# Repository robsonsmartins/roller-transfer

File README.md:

# PCB Roller Transfer Machine
The PCB Roller Transfer Machine (or Laminator Machine) is a machine designed to thermally transfer toner printed on paper to a blank Printed Circuit Board.

Project site: [PCB Roller Transfer Machine Project](https://www.robsonmartins.com/content/eletr/projects/laminadora/)

[![CC BY-NC-SA 4.0][cc-by-nc-sa-shield]][cc-by-nc-sa]

This work is licensed under a
[Creative Commons Attribution-NonCommercial-ShareAlike 4.0 International License][cc-by-nc-sa].

[![CC BY-NC-SA 4.0][cc-by-nc-sa-image]][cc-by-nc-sa]

[cc-by-nc-sa]: http://creativecommons.org/licenses/by-nc-sa/4.0/
[cc-by-nc-sa-image]: https://licensebuttons.net/l/by-nc-sa/4.0/88x31.png
[cc-by-nc-sa-shield]: https://img.shields.io/badge/License-CC%20BY--NC--SA%204.0-lightgrey.svg

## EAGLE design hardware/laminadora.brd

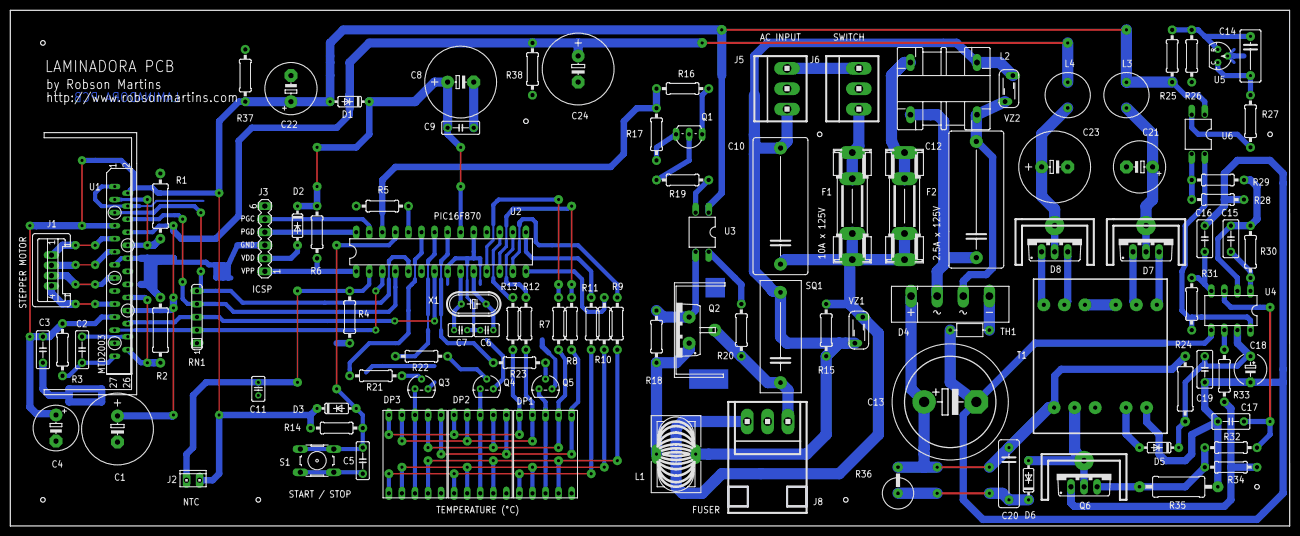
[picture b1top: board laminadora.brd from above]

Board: 2 copper layers, 248.5 x 99.9 mm, 105 parts (0 on the bottom side), 87 nets.

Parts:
C1: 2200uF x 16V; E5-13
C2: 3n3; C050-025X075
C3, C5, C9: 100nF; C050-025X075
C4: 470uF x 10V; E5-8,5
C6, C7: 15pF; C025-025X050
C8: 2200uF x 10V; E5-13
C10, C12: 220nF x 250V; C225-108X268
C11: 1nF; C025-025X050
C13: 330uF x 200V; EB22,5D
C14: 330nF; C075-042X103
C15: 2n7; C050-030X075
C16: 2n2; C050-030X075
C17: 10nF; C050-030X075
C18: 47uF x 25V; E5-6
C19: 100nF; C050-030X075
C20: 10nF x 400V; C102-043X133
C21, C22: 1000uF x 10V; E5-10,5
C23: 1000uF x 25V; E5-13
C24: 2200uF x 25V; E5-13
D1, D5, D6: 1N3613; DO35-7
D2, D3: 1N4148; DO35-7
D4: D2SBA-60; FBU4
D7, D8: F10SC4R; TO220ABS
DP1, DP2, DP3: HD-H103; HDSP-M
F1: 10A; SHK20L
F2: 2.5A; SHK20L
J1: A20-04
J2: A20-04; 10X02MTA
J3: MA06-1
J5, J6, J8: 794681-2; 1X3MTA
L1: 80uH; A26GFC
L2: MFE
L3, L4: 4.7uH; 6000-XXXX-RC
Q1: 2SC1740; TO92-ECB
Q2: BCR8PM; TO220BVSINK
Q3, Q4, Q5: BC547; TO92
Q6: FS7UM; TO220BV
R1, R2: 0R47; 0309/12
R3: 20K; 0207/10
R4: 5K6 x 1%; 0207/10
R5, R6, R14, R31: 10K; 0207/10
R7, R8, R9, R10, R11, R12, R13, R37: 100R; 0207/10
R15: 1M; 0207/10
R16: 100K; 0207/10
R17, R34: 2K2; 0207/10
R18, R19, R27: 150R; 0207/10
R20, R33: 22R; 0207/10
R21, R22, R23, R38: 1K; 0207/10
R24: 56K x 1W; 0309/12
R25, R26: 3K9 x 1%; 0207/10
R28: 270R; 0207/10
R29, R30: 3K9; 0207/10
R32: 56R; 0207/10
R35: 0R33 x 2W; 0411/15
R36: 22K x 7W; 0617V
RN1: 10K; SIL5
S1: B3F-10XX
SQ1: AU1201; AU
T1: SK69ABD2
TH1: BR207; R-7,5
U1: MTD2003; ZIP27SINK
U2: PIC16F870P; DIL28-3
U3: S21ME6; DIL4
U4: UC3842N; DIL08
U5: TL431; TO92-CLP
U6: PS2501; DIL04
VZ1, VZ2: V7471U; S05K17
X1: 20MHz; HC49U-V

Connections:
5VNR: C21.+, D7.C, L3.1
12VNR: C23.+, D8.C, L4.1
+5V: C3.1, C4.+, C22.+, D1.A, D3.C, J2.1, L3.2, R3.2, R14.2, R25.2, R37.2, U1.2, U1.7, U1.21, U3.1, U6.1
+12V: C1.+, C24.+, L4.2, R38.2, U1.8, U1.20
+150V: C13.+, C20.1, D4.+, R24.2, R36.2, T1.1
A: R7.2, U2.11
AC_COM: C10.2, J5.3, L1.1, L2.4, R15.1, SQ1.1, VZ1.1, VZ2.1
AC_FUSER: J8.3, Q2.T2, R20.2, SQ1.2
AC_IN: J5.1, J6.1
AC_OUT: C10.1, F1.2A, F2.1A, J8.1, R15.2, VZ1.2
AC_SW: F1.1A, J6.3
AGND: C13.-, C16.2, C17.2, C18.-, C19.2, R28.1, R35.1, T1.4, TH1.1, U4.5
B: R8.2, U2.12
C: R9.2, U2.13
CONTROL: R16.2, R17.2, U2.26
CR: C2.1, R3.1, U1.27
D: R10.2, U2.14
DA: DP1.7, DP2.7, DP3.7, R7.1
DB: DP1.6, DP2.6, DP3.6, R8.1
DC: DP1.4, DP2.4, DP3.4, R9.1
DD: DP1.2, DP2.2, DP3.2, R10.1
DE: DP1.1, DP2.1, DP3.1, R11.1
DF: DP1.9, DP2.9, DP3.9, R12.1
DG: DP1.10, DP2.10, DP3.10, R13.1
E: R11.2, U2.15
F: R12.2, U2.16
G: R13.2, U2.17
GATE: Q2.G, R18.2, U3.3
GND: C1.-, C2.2, C3.2, C4.-, C5.2, C6.2, C7.2, C8.-, C9.2, C11.2, C21.-, C22.-, C23.-, C24.-, J3.3, Q1.E, Q3.1, Q4.1, Q5.1, R1.1, R2.1, R4.1, R5.1, R16.1, R26.1, R37.1, R38.1, RN1.1, S1.1, S1.2, T1.7, T1.8, U1.1, U1.4, U1.13, U1.24, U2.8, U2.19, U5.A
IN1: RN1.4, U1.6, U2.4
IN2: RN1.5, U1.5, U2.5
IN3: RN1.2, U1.23, U2.3
IN4: RN1.3, U1.22, U2.7
K0: R23.2, U2.21
K1: R22.2, U2.22
K2: R21.2, U2.23
unnamed: DP3.3, DP3.8, Q3.3
unnamed: DP2.3, DP2.8, Q4.3
unnamed: DP1.3, DP1.8, Q5.3
unnamed: R20.1, U3.4
unnamed: Q5.2, R23.1
unnamed: Q4.2, R22.1
unnamed: L1.2, Q2.T1, R18.1
unnamed: R19.2, U3.2
unnamed: Q3.2, R21.1
unnamed: Q1.C, R19.1
unnamed: Q1.B, R17.1
unnamed: F2.2A, L2.1
unnamed: R27.1, U6.2
unnamed: R28.2, R29.2, U6.3
unnamed: C14.2, R27.2, U5.C
unnamed: C14.1, R25.1, R26.2, U5.R
unnamed: D7.A1, T1.6
unnamed: C20.2, D6.C, R36.1
unnamed: D5.A, T1.3
unnamed: D7.A2, T1.5
unnamed: D8.A1, T1.10
unnamed: D8.A2, T1.9
NTC: C11.1, J2.2, R4.2, U2.2
OUT1: J1.1, U1.9
OUT2: J1.2, U1.11
OUT3: J1.3, U1.15
OUT4: J1.4, U1.19
PGC: J3.5, U2.27
PGD: J3.4, U2.28
PGM: R5.2, U2.24
PWR_16VCC: C18.+, C19.1, D5.C, R24.1, U4.7
PWR_AC1: C12.1, D4.AC1, L2.2
PWR_AC2: C12.2, D4.AC2, L2.3, VZ2.2
PWR_COMP: C15.1, R30.2, U4.1
PWR_D_FET: D6.A, Q6.D, T1.2
PWR_FET_OUT: R33.2, U4.6
PWR_G_FET: Q6.G, R33.1, R34.2
PWR_ISENSE: C17.1, R32.2, U4.3
PWR_RTCT: C16.1, R31.1, U4.4
PWR_S_FET: Q6.S, R32.1, R34.1, R35.2
PWR_VFB: C15.2, R29.1, R30.1, U4.2
PWR_VNEG: D4.-, TH1.2
PWR_VREF: R31.2, U4.8, U6.4
SA: R1.2, U1.3, U1.10
SB: R2.2, U1.18, U1.26
START_STOP: C5.1, D3.A, R14.1, S1.3, S1.4, U2.25
VDD: D2.A, J3.2
VDD_MICRO: C8.+, C9.1, D1.C, D2.C, R6.2, U2.20
VPP: J3.1, R6.1, U2.1
XTAL1: C7.1, U2.9, X1.2
XTAL2: C6.1, U2.10, X1.1

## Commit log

2021-12-21 Initial version (1.0a)
